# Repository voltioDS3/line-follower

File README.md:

# line-follower
Repo en el cual se desarrolla un seguidor de linea

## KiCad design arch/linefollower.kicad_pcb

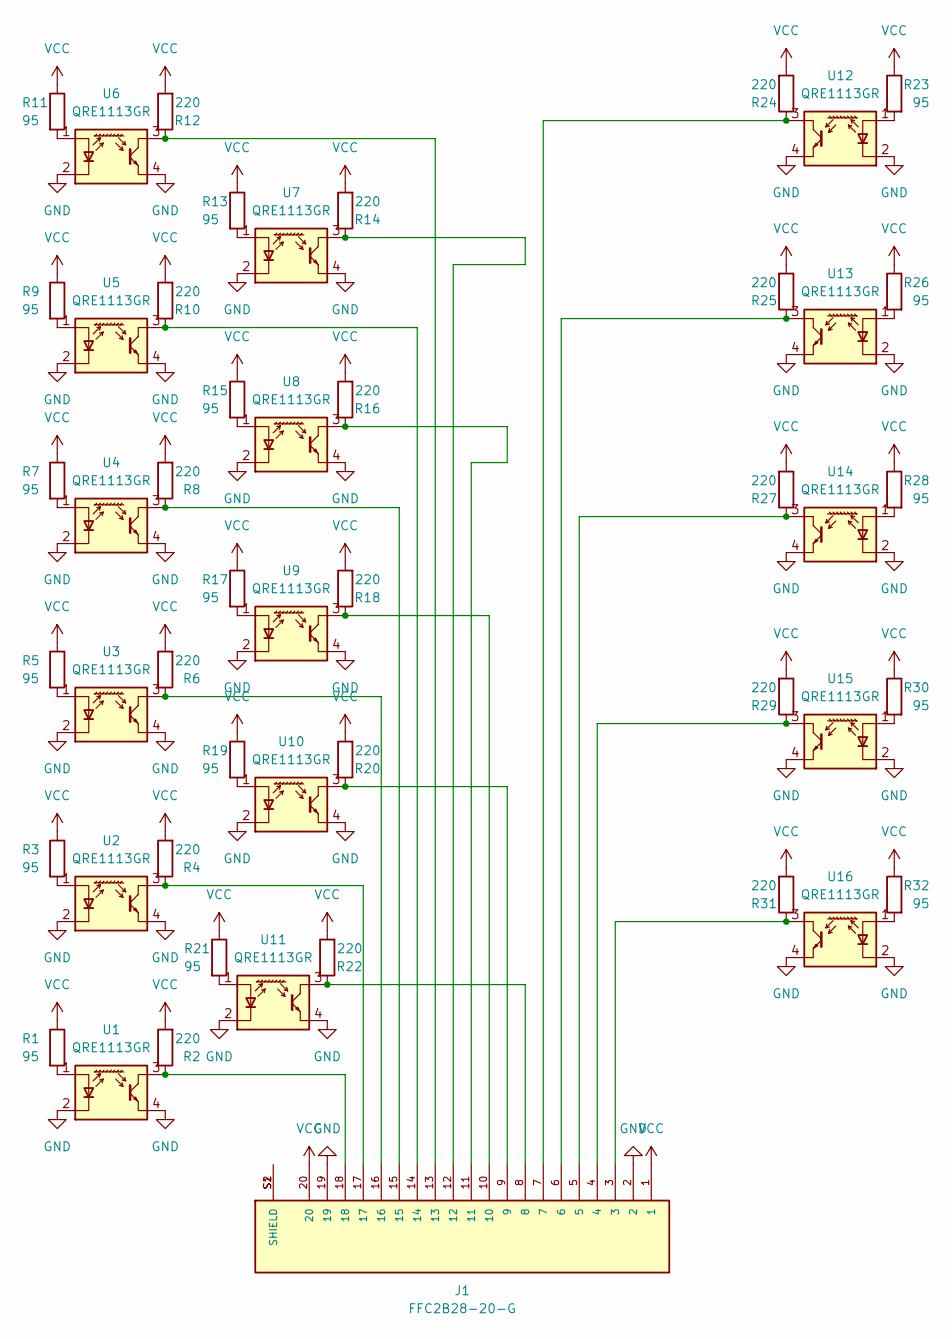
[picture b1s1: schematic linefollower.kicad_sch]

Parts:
J1: FFC2B28-20-G; Hirose_FH12-20S-0.5SH_1x20-1MP_P0.50mm_Horizontal; PARTREV A
R1, R3, R5, R7, R9, R11, R13, R15, R17, R19, R21, R23, R26, R28, R30, R32: 95; R_0603_1608Metric_Pad0.98x0.95mm_HandSolder
R2, R4, R6, R8, R10, R12, R14, R16, R18, R20, R22, R24, R25, R27, R29, R31: 220; R_0603_1608Metric_Pad0.98x0.95mm_HandSolder
U1, U2, U3, U4, U5, U6, U7, U8, U9, U10, U11, U12, U13, U14, U15, U16: QRE1113GR; OnSemi_CASE100CY

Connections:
GND: J1.2, J1.19, U1.2 (K), U1.4, U2.2 (K), U2.4, U3.2 (K), U3.4, U4.2 (K), U4.4, U5.2 (K), U5.4, U6.2 (K), U6.4, U7.2 (K), U7.4, U8.2 (K), U8.4, U9.2 (K), U9.4, U10.2 (K), U10.4, U11.2 (K), U11.4, U12.2 (K), U12.4, U13.2 (K), U13.4, U14.2 (K), U14.4, U15.2 (K), U15.4, U16.2 (K), U16.4
unnamed: J1.3, R31.1, U16.3
unnamed: J1.4, R29.1, U15.3
unnamed: J1.5, R27.1, U14.3
unnamed: J1.6, R25.1, U13.3
unnamed: J1.7, R24.1, U12.3
unnamed: J1.8, R22.1, U11.3
unnamed: J1.9, R20.1, U10.3
unnamed: J1.10, R18.1, U9.3
unnamed: J1.11, R16.1, U8.3
unnamed: J1.12, R14.1, U7.3
unnamed: J1.13, R12.1, U6.3
unnamed: J1.14, R10.1, U5.3
unnamed: J1.15, R8.1, U4.3
unnamed: J1.16, R6.1, U3.3
unnamed: J1.17, R4.1, U2.3
unnamed: J1.18, R2.1, U1.3
unnamed: R1.2, U1.1 (A)
unnamed: R3.2, U2.1 (A)
unnamed: R5.2, U3.1 (A)
unnamed: R7.2, U4.1 (A)
unnamed: R9.2, U5.1 (A)
unnamed: R11.2, U6.1 (A)
unnamed: R13.2, U7.1 (A)
unnamed: R15.2, U8.1 (A)
unnamed: R17.2, U9.1 (A)
unnamed: R19.2, U10.1 (A)
unnamed: R21.2, U11.1 (A)
unnamed: R23.2, U12.1 (A)
unnamed: R26.2, U13.1 (A)
unnamed: R28.2, U14.1 (A)
unnamed: R30.2, U15.1 (A)
unnamed: R32.2, U16.1 (A)
VCC: J1.1, J1.20, R1.1, R2.2, R3.1, R4.2, R5.1, R6.2, R7.1, R8.2, R9.1, R10.2, R11.1, R12.2, R13.1, R14.2, R15.1, R16.2, R17.1, R18.2, R19.1, R20.2, R21.1, R22.2, R23.1, R24.2, R25.2, R26.1, R27.2, R28.1, R29.2, R30.1, R31.2, R32.1

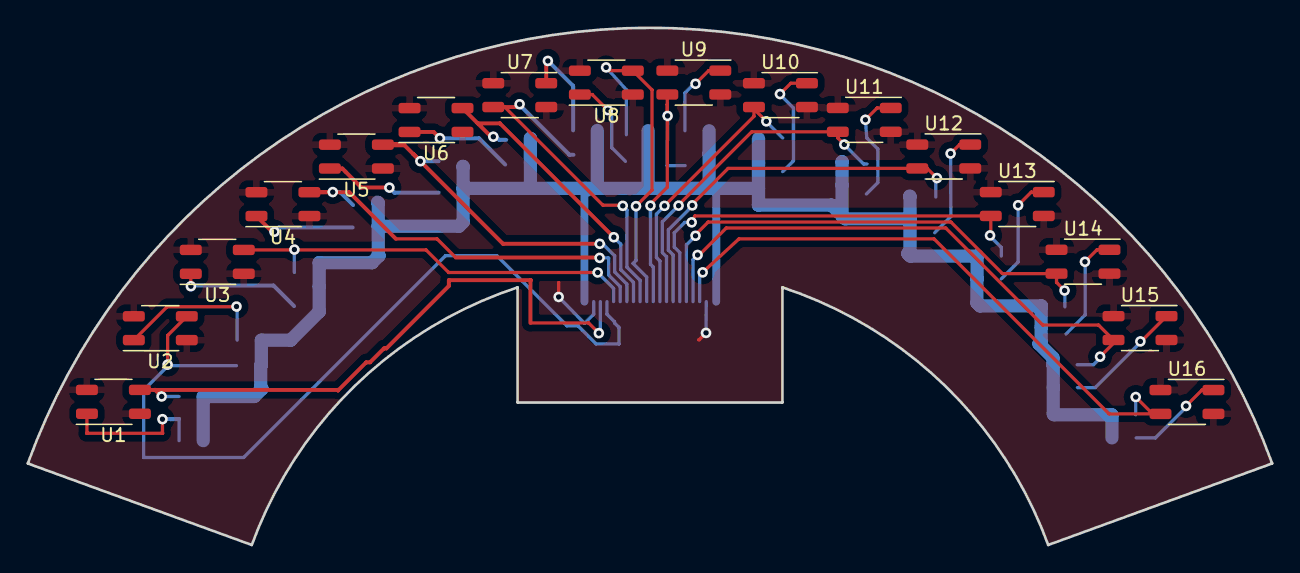
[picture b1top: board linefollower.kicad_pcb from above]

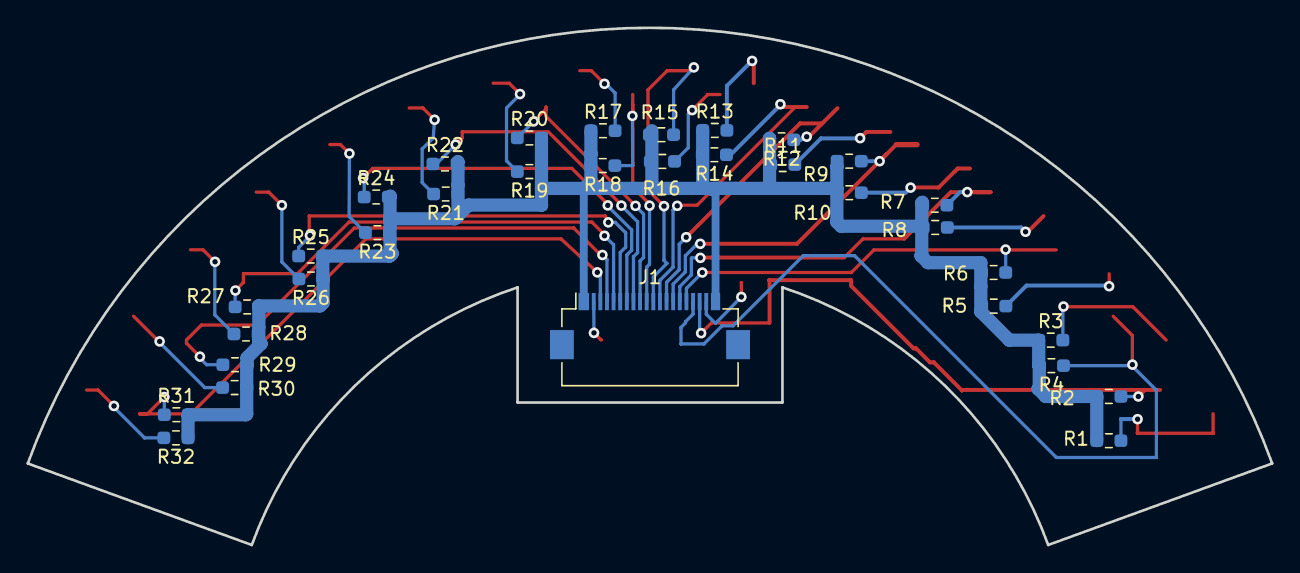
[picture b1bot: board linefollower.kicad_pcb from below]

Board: 2 copper layers, 94.0 x 39.1 mm, 49 parts (33 on the bottom side), 34 nets.

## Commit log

2024-03-21 added arch files
2024-03-22 update pcb
2024-04-01 arco con silkscreen corregida
